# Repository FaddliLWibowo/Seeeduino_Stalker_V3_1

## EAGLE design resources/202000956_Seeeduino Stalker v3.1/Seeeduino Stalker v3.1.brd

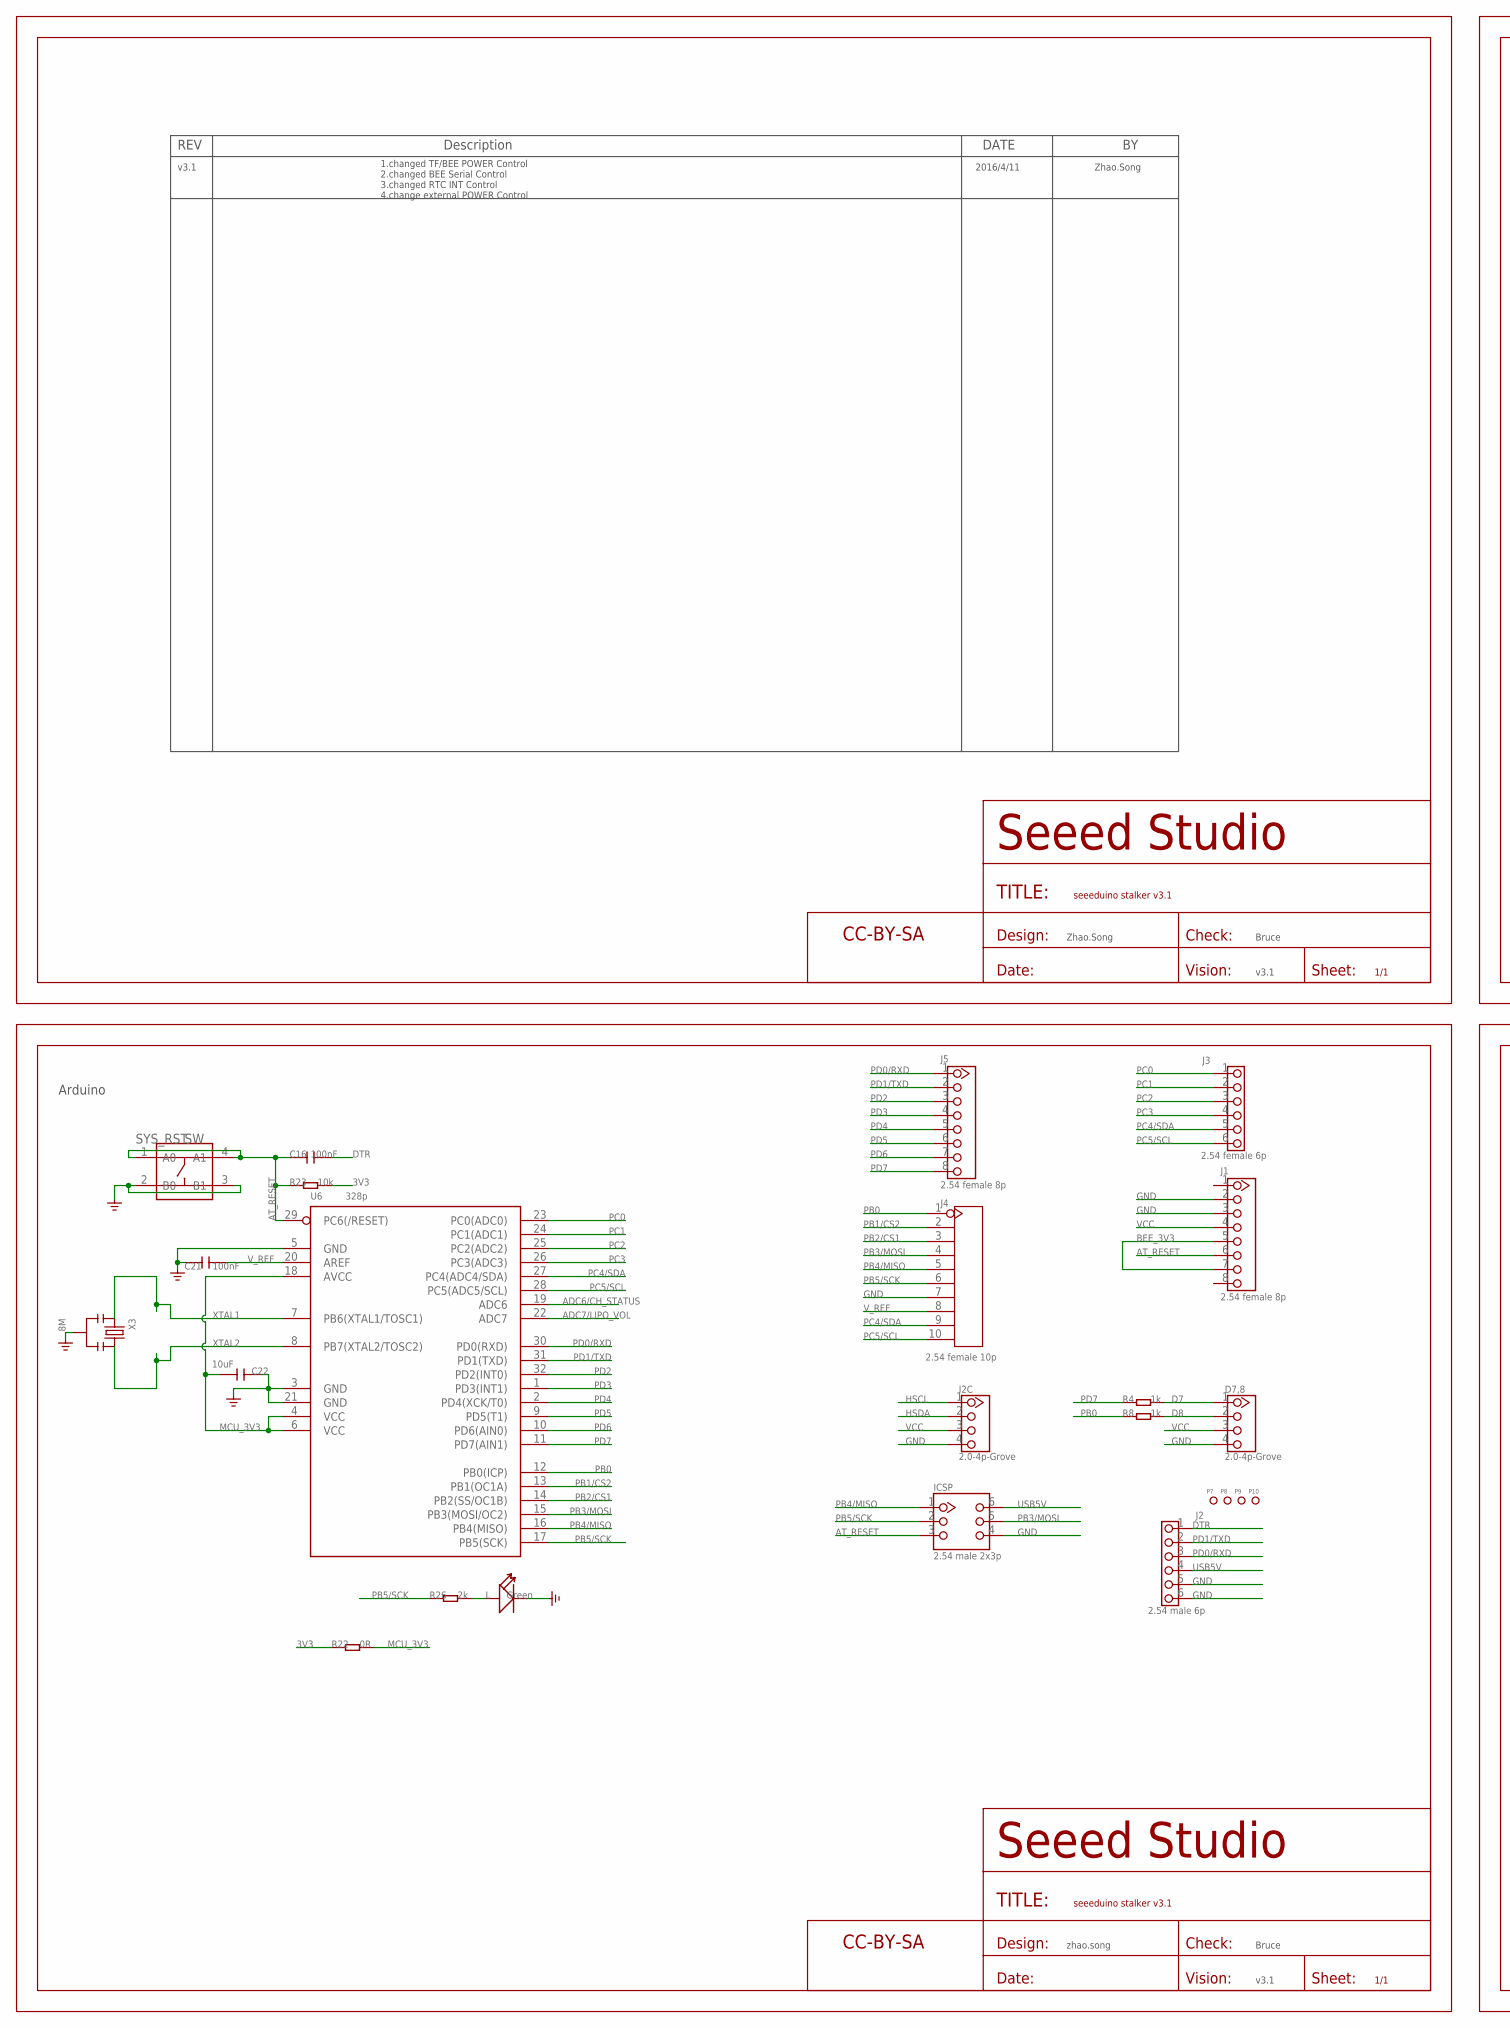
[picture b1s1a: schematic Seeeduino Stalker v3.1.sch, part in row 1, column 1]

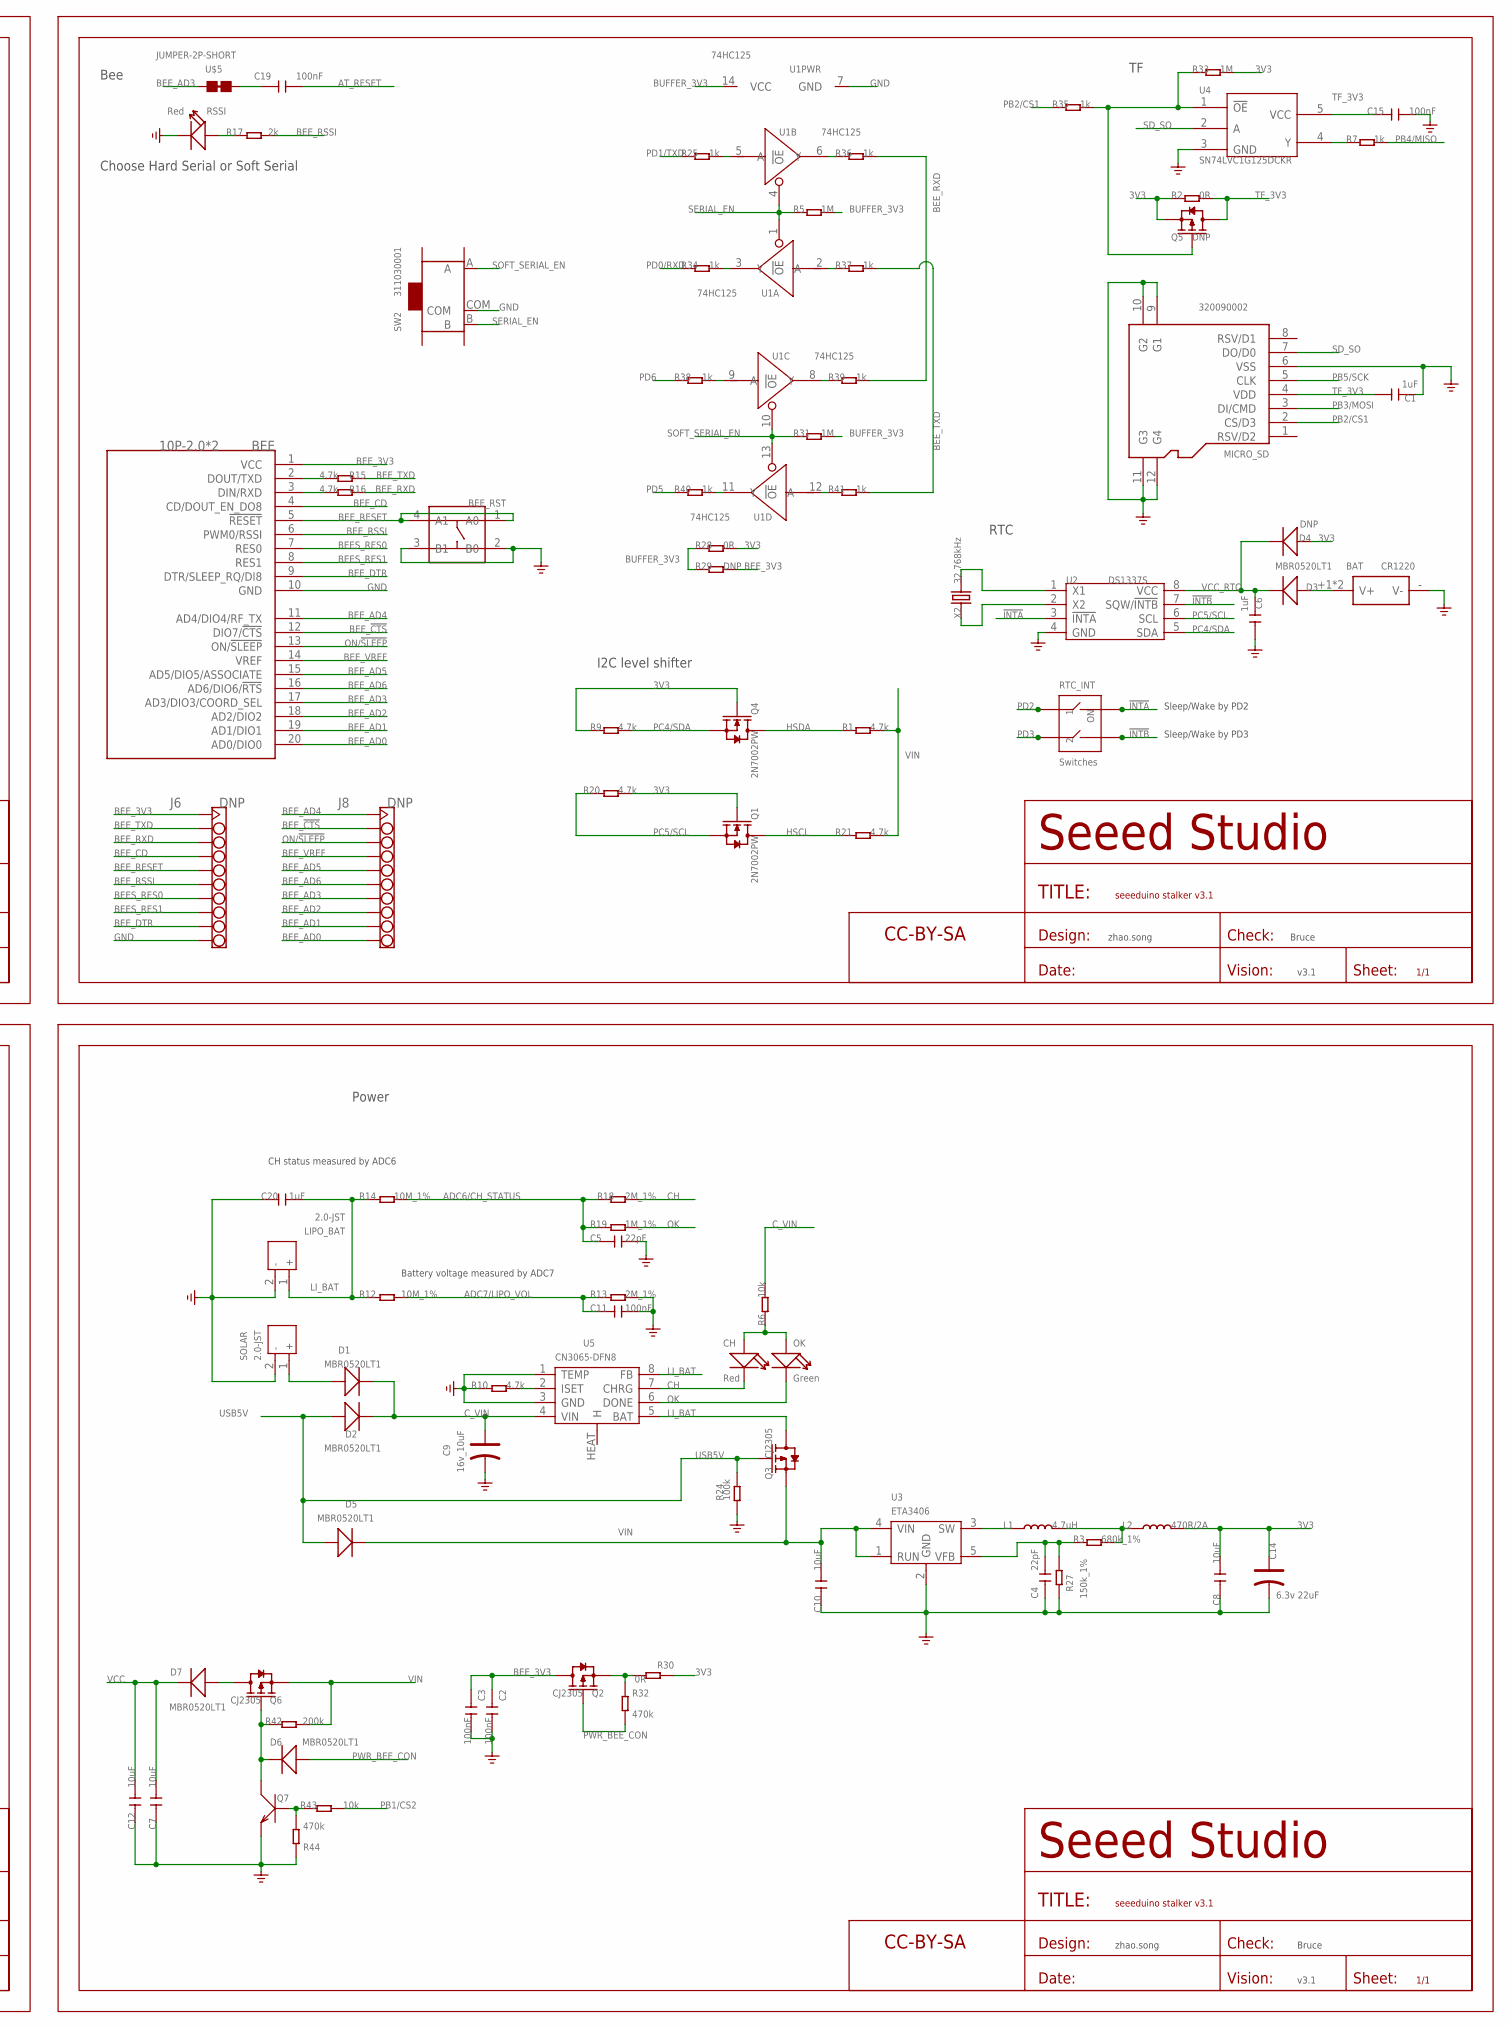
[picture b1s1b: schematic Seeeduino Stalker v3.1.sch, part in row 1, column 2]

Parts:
BAT: CR1220; BAT2P-13.5-CR1220
BEE: 10P-2.0*2; BEE
BEE_RST: SW; 4P-SMD-6.2X6.2X4H
C1, C6, C20: 1uF; C0805
C2, C3, C11, C15, C16, C19, C21: 100nF; C0603
C4, C5: 22pF; C0603
C7, C8, C10, C12, C22: 10uF; C0805
C9: 16v_10uF; AVX-A
C14: 6.3v 22uF; AVX-A
CH: Red; D0603
D1, D2, D3, D5, D6, D7: MBR0520LT1; SOD123-2.7X1.6
D4: DNP; SOD123-2.7X1.6
D7,8: 2.0-4p-Grove; 4P-2.0
I2C: 2.0-4p-Grove; 4P-2.0
ICSP: 2.54 male 2x3p; 2X3P-2.54-LEADED
J1, J5: 2.54 female 8p; 8P-2.54-LEADED
J2: 2.54 male 6p; 6P-2.54-LEADED
J3: 2.54 female 6p; 6P-2.54-LEADED
J4: 2.54 female 10p; 10P-2.54
J6, J8: DNP; HEADER_1X10
L: Green; D0603
L1: 4.7uH; L0420
L2: 470R/2A; L0805
LIPO_BAT: 2.0-JST; JST-2.0
MICRO_SD: 320090002; MICRO-SD8+4P-SMD-14.5X13.6X1.8MM
OK: Green; D0603
P7, P8, P9, P10: DNP; ROUND-MARK-1.0
Q1, Q4: 2N7002PW; SOT23
Q2, Q3, Q6: CJ2305; SOT23
Q5: DNP; SOT23
Q7: TRANSISTOR-NPN-SOT23; SOT-23
R1, R9, R10, R15, R16, R20, R21: 4.7k; 0603@1
R2, R22, R28, R30: 0R; 0603@1
R3: 680k_1%; 0603@1
R4, R7, R8, R25, R34, R35, R36, R37, R38, R39, R40, R41: 1k; 0603@1
R5, R31, R33: 1M; 0603@1
R6, R23, R43: 10k; 0603@1
R12, R14: 10M_1%; 0603@1
R13, R18: 2M_1%; 0603@1
R17, R26: 2k; 0603@1
R19: 1M_1%; 0603@1
R24: 100k; 0603@1
R27: 150k_1%; 0603@1
R29: DNP; 0603@1
R32, R44: 470k; 0603@1
R42: 200k; 0603@1
RSSI: Red; D0603
RTC_INT: Switches; SW4-SMD-2.54-5.08X6.8X3.3MM
SOLAR: 2.0-JST; JST-2.0
SW2: 311030001; SW7-SMD-L6.7X2.7X3.2MM
SYS_RST: SW; 4P-SMD-6.2X6.2X4H
U1: 74HC125; TSSOP14-0.65-5X4.4MM
U2: DS1337S; SOP8
U3: ETA3406; SOT23-5
U4: SN74LVC1G125DCKR; SOT353
U5: CN3065-DFN8; DFN8
U6: 328p; TQFP32-0.8-7X7MM
U$2, U$11, U$12, U$27: DNP; SEEEDSTUDIO-PCB-FRAME
U$5: JUMPER-2P-SHORT; 2P-SMD-SHORT
X2: 32.768kHz; 2P-SMD-3.2X1.5
X3: 8M; RESONATOR3-SMD-3.6X1.3X0.8MM

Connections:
3V3: C8.2, C14.+, D4.1 (+), L2.2, Q1.1 (G), Q4.1 (G), Q5.2 (S), R2.1, R9.1, R20.2, R22.1, R23.2, R28.2, R30.1, R33.2
!INTA: RTC_INT.4, U2.3 (!INTA)
!INTB: RTC_INT.3, U2.7 (SQW/!INTB)
ADC6/CH_STATUS: C5.1, R14.2, R18.1, R19.1, U6.19 (ADC6)
ADC7/LIPO_VOL: C11.1, R12.2, R13.1, U6.22 (ADC7)
AT_RESET: C16.1, C19.2, ICSP.3, J1.6, R23.1, SYS_RST.1 (A0), SYS_RST.4 (A1), U6.29 (PC6(/RESET))
BEES_RES0: BEE.7 (RES0), J6.7
BEES_RES1: BEE.8 (RES1), J6.8
BEE_3V3: BEE.1 (VCC), C2.1, C3.1, J1.5, J1.7, J6.1, Q2.3 (D), R29.2
BEE_!CTS: BEE.12 (DIO7/!CTS), J8.2
BEE_AD0: BEE.20 (AD0/DIO0), J8.10
BEE_AD1: BEE.19 (AD1/DIO1), J8.9
BEE_AD2: BEE.18 (AD2/DIO2), J8.8
BEE_AD3: BEE.17 (AD3/DIO3/COORD_SEL), J8.7, U$5.1
BEE_AD4: BEE.11 (AD4/DIO4/RF_TX), J8.1
BEE_AD5: BEE.15 (AD5/DIO5/ASSOCIATE), J8.5
BEE_AD6: BEE.16 (AD6/DIO6/!RTS), J8.6
BEE_CD: BEE.4 (CD/DOUT_EN_DO8), J6.4
BEE_DTR: BEE.9 (DTR/SLEEP_RQ/DI8), J6.9
BEE_RESET: BEE.5 (!RESET), BEE_RST.1 (A0), BEE_RST.4 (A1), J6.5
BEE_RSSI: BEE.6 (PWM0/RSSI), J6.6, R17.2
BEE_RXD: J6.3, R16.1, R36.2, R39.2
BEE_TXD: J6.2, R15.1, R37.2, R41.2
BEE_VREF: BEE.14 (VREF), J8.4
BUFFER_3V3: R5.2, R28.1, R29.1, R31.2, U1.14 (VCC)
CH: CH.-, R18.2, U5.7 (CHRG)
C_VIN: C9.+, D1.2 (-), D2.2 (-), R6.2, U5.4 (VIN)
D7: D7,8.1, R4.2
D8: D7,8.2, R8.2
DTR: C16.2, J2.1
GND: BAT.- (V-), BEE.10 (GND), BEE_RST.2 (B0), BEE_RST.3 (B1), C1.1, C2.2, C3.2, C4.1, C5.2, C6.2, C7.1, C8.1, C9.-, C10.1, C11.2, C12.1, C14.-, C15.2, C20.1, C21.1, C22.1, D7,8.4, I2C.4, ICSP.4, J1.2, J1.3, J2.5, J2.6, J4.7, J6.10, L.-, LIPO_BAT.2, MICRO_SD.6 (VSS), MICRO_SD.9 (G1), MICRO_SD.10 (G2), MICRO_SD.11 (G3), MICRO_SD.12 (G4), Q7.2 (E), R10.1, R13.2, R24.1, R27.1, R44.2, RSSI.-, SOLAR.2, SW2.COM, SYS_RST.2 (B0), SYS_RST.3 (B1), U1.7 (GND), U2.4 (GND), U3.2 (GND), U4.3 (GND), U5.1 (TEMP), U5.3 (GND), U6.3 (GND), U6.5 (GND), U6.21 (GND), X3.2
HSCL: I2C.1, Q1.3 (D), R21.1
HSDA: I2C.2, Q4.3 (D), R1.1
LI_BAT: C20.2, LIPO_BAT.1, Q3.3 (D), R12.1, R14.1, U5.5 (BAT), U5.8 (FB)
MCU_3V3: C22.2, R22.2, U6.4 (VCC), U6.6 (VCC), U6.18 (AVCC)
unnamed: C4.2, R3.1, R27.2, U3.5 (VFB)
unnamed: C19.1, U$5.2
unnamed: D1.1 (+), SOLAR.1
unnamed: BAT.+1 (V+), BAT.+2 (V+), D3.1 (+)
unnamed: R10.2, U5.2 (ISET)
unnamed: R17.1, RSSI.+
unnamed: U2.1 (X1), X2.2
unnamed: CH.+, OK.+, R6.1
unnamed: U2.2 (X2), X2.1
unnamed: R34.2, U1.3 (Y)
unnamed: D7.1 (+), Q6.3 (D)
unnamed: R38.2, U1.9 (A)
unnamed: Q7.1 (B), R43.2, R44.1
unnamed: L1.2, L2.1, R3.2
unnamed: L1.1, U3.3 (SW)
unnamed: R7.1, U4.4 (Y)
unnamed: R40.2, U1.11 (Y)
unnamed: L.+, R26.2
unnamed: R36.1, U1.6 (Y)
unnamed: BEE.2 (DOUT/TXD), R15.2
unnamed: BEE.3 (DIN/RXD), R16.2
unnamed: R37.1, U1.2 (A)
unnamed: R39.1, U1.8 (Y)
unnamed: R41.1, U1.12 (A)
unnamed: R25.2, U1.5 (A)
unnamed: Q2.2 (S), R30.2, R32.1
unnamed: Q5.1 (G), R33.1, R35.2, U4.1 (!OE!)
unnamed: D6.2 (-), Q6.1 (G), Q7.3 (C), R42.2
OK: OK.-, R19.2, U5.6 (DONE)
ON/!SLEEP: BEE.13 (ON/!SLEEP), J8.3
PB0: J4.1, R8.1, U6.12 (PB0(ICP))
PB1/CS2: J4.2, R43.1, U6.13 (PB1(OC1A))
PB2/CS1: J4.3, MICRO_SD.2 (CS/D3), R35.1, U6.14 (PB2(SS/OC1B))
PB3/MOSI: ICSP.5, J4.4, MICRO_SD.3 (DI/CMD), U6.15 (PB3(MOSI/OC2))
PB4/MISO: ICSP.1, J4.5, R7.2, U6.16 (PB4(MISO))
PB5/SCK: ICSP.2, J4.6, MICRO_SD.5 (CLK), R26.1, U6.17 (PB5(SCK))
PC0: J3.1, U6.23 (PC0(ADC0))
PC1: J3.2, U6.24 (PC1(ADC1))
PC2: J3.3, U6.25 (PC2(ADC2))
PC3: J3.4, U6.26 (PC3(ADC3))
PC4/SDA: J3.5, J4.9, Q4.2 (S), R9.2, U2.5 (SDA), U6.27 (PC4(ADC4/SDA))
PC5/SCL: J3.6, J4.10, Q1.2 (S), R20.1, U2.6 (SCL), U6.28 (PC5(ADC5/SCL))
PD0/RXD: J2.3, J5.1, R34.1, U6.30 (PD0(RXD))
PD1/TXD: J2.2, J5.2, R25.1, U6.31 (PD1(TXD))
PD2: J5.3, RTC_INT.1, U6.32 (PD2(INT0))
PD3: J5.4, RTC_INT.2, U6.1 (PD3(INT1))
PD4: J5.5, U6.2 (PD4(XCK/T0))
PD5: J5.6, R40.1, U6.9 (PD5(T1))
PD6: J5.7, R38.1, U6.10 (PD6(AIN0))
PD7: J5.8, R4.1, U6.11 (PD7(AIN1))
PWR_BEE_CON: D6.1 (+), Q2.1 (G), R32.2
SD_SO: MICRO_SD.7 (DO/D0), U4.2 (A)
SERIAL_EN: R5.1, SW2.B, U1.1 (!OE), U1.4 (!OE)
SOFT_SERIAL_EN: R31.1, SW2.A, U1.10 (!OE), U1.13 (!OE)
TF_3V3: C1.2, C15.1, MICRO_SD.4 (VDD), Q5.3 (D), R2.2, U4.5 (VCC)
USB5V: D2.1 (+), D5.1 (+), ICSP.6, J2.4, Q3.1 (G), R24.2
VCC: C7.2, C12.2, D7.2 (-), D7,8.3, I2C.3, J1.4
VCC_RTC: C6.1, D3.2 (-), D4.2 (-), U2.8 (VCC)
VIN: C10.2, D5.2 (-), Q3.2 (S), Q6.2 (S), R1.2, R21.2, R42.1, U3.1 (RUN), U3.4 (VIN)
V_REF: C21.2, J4.8, U6.20 (AREF)
XTAL1: U6.7 (PB6(XTAL1/TOSC1)), X3.1
XTAL2: U6.8 (PB7(XTAL2/TOSC2)), X3.3

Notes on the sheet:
Power
Arduino
Bee
Battery voltage measured by ADC7
RTC
Sleep/Wake by PD2
Sleep/Wake by PD3
CH status measured by ADC6
Choose Hard Serial or Soft Serial
zhao.song
Bruce
v3.1
2016/4/11
Zhao.Song
1.changed TF/BEE POWER Control 2.changed BEE Serial Control 3.changed RTC INT Control 4.change external POWER Control
I2C level shifter

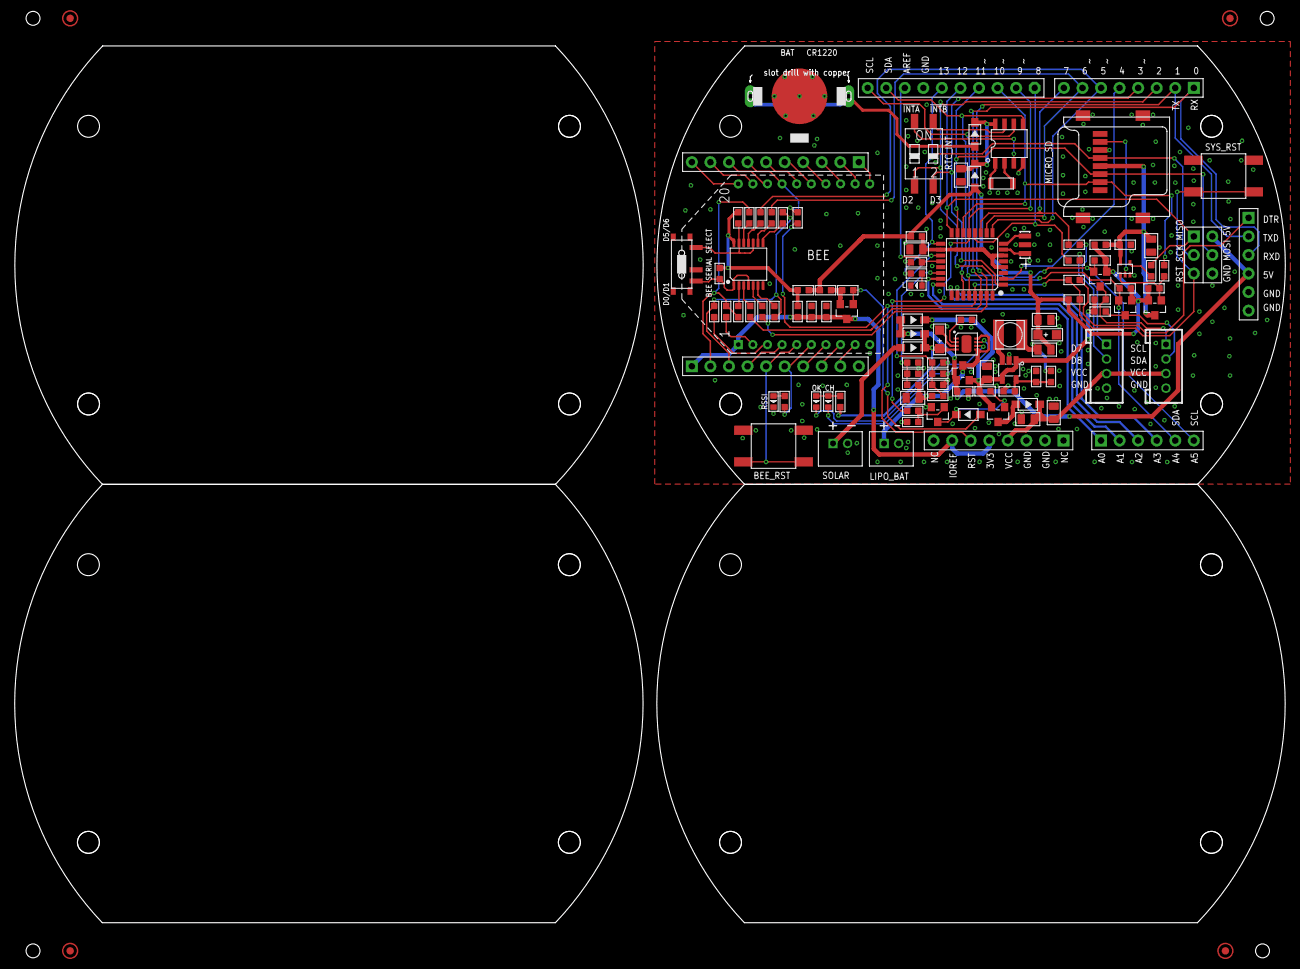
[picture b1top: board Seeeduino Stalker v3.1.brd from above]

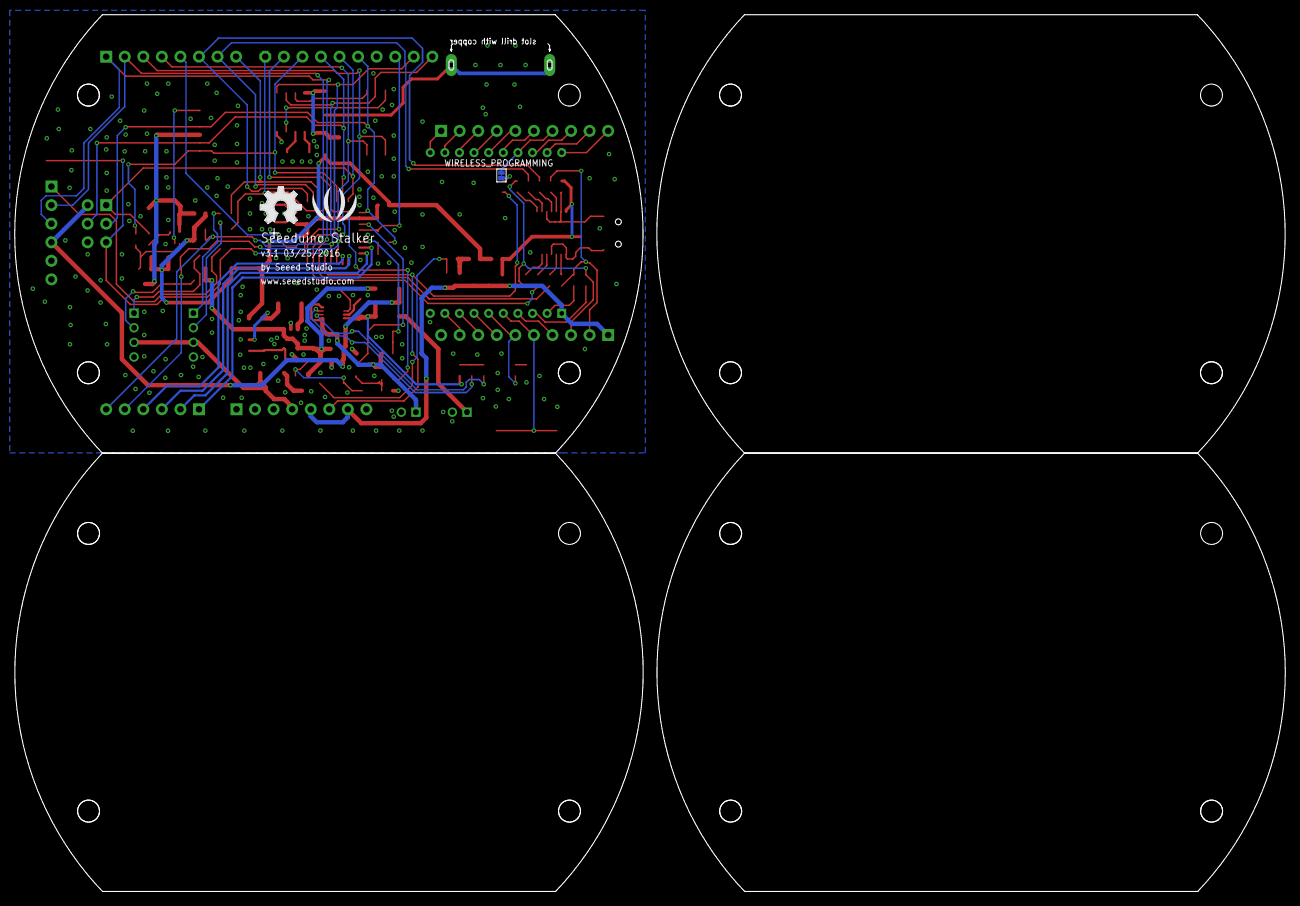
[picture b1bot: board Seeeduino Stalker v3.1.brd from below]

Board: 2 copper layers, 173.9 x 120.0 mm, 120 parts (3 on the bottom side), 97 nets.

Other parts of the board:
U$23: OSHW_FILLX200_NOTEXT
U$24: LOGO_SILK

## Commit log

2016-07-26 add file
2016-07-27 add cover.jpg
2016-07-27 add iamge
2016-07-28 add pinmap
2016-07-29 add bees image
2016-07-29 add set sketch image

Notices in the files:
parts and their libraries:
moudle-new: This work is licensed under the Creative Commons Attribution 4.0 International License.
To view a copy of this license,visit:
http://creativecommons.org/licenses/by-sa/4.0
moudle-new: CC-BY-SA
